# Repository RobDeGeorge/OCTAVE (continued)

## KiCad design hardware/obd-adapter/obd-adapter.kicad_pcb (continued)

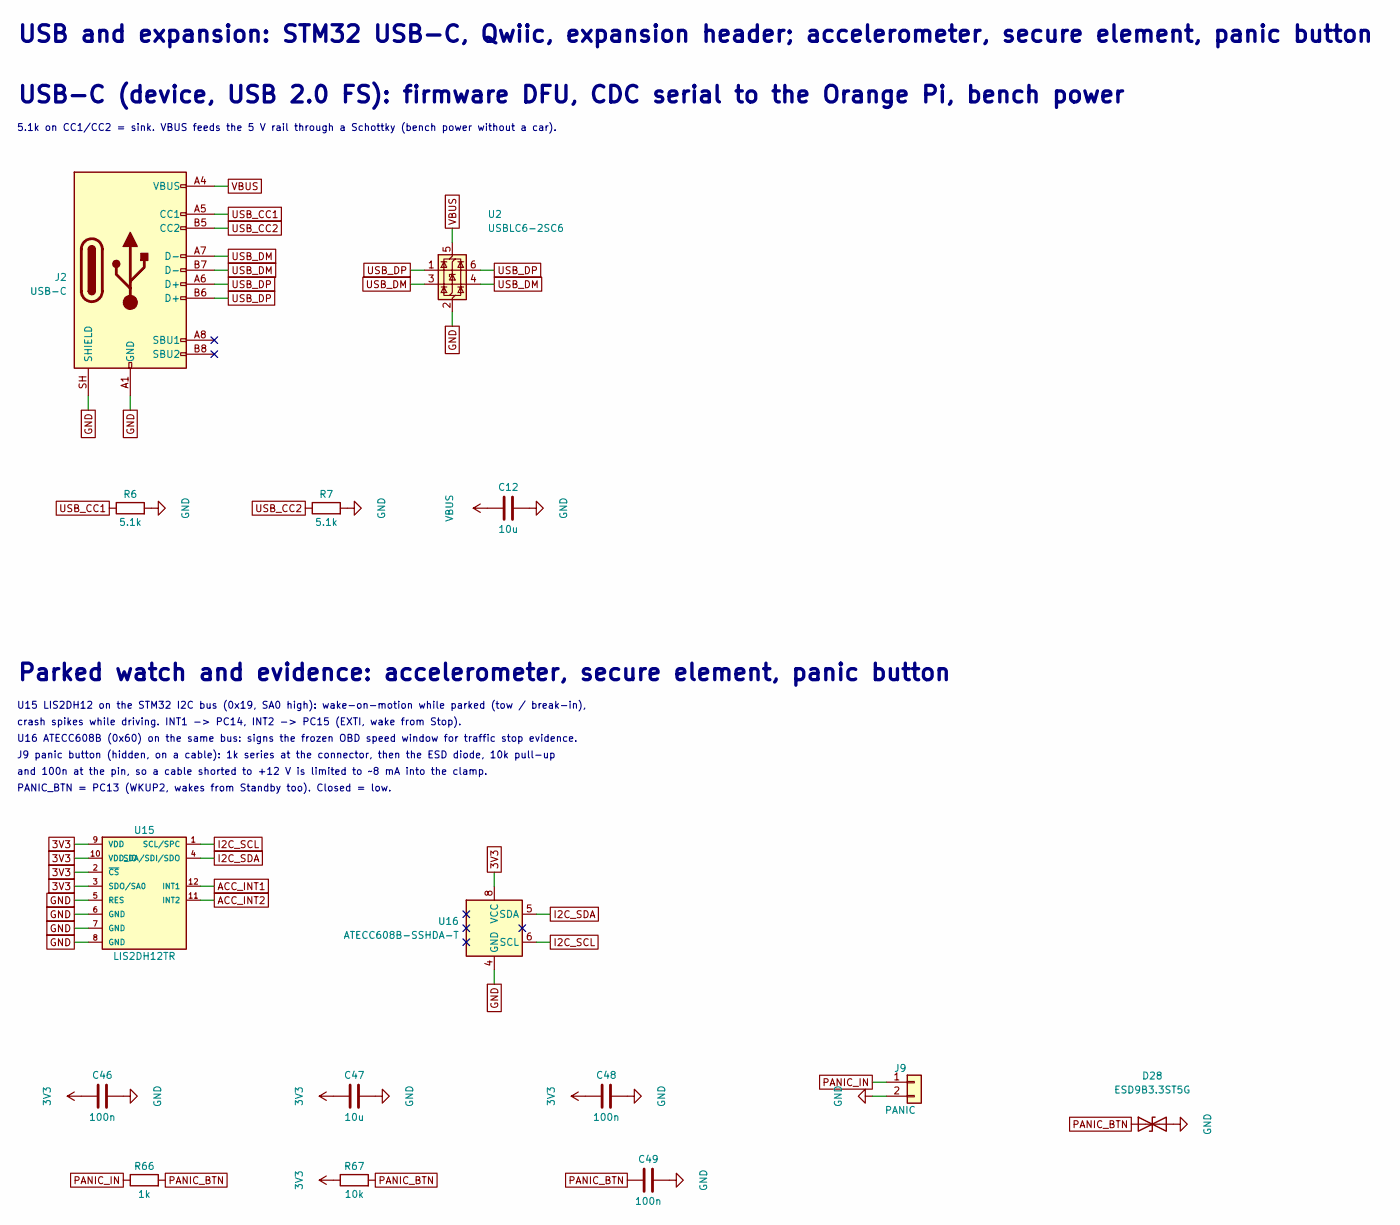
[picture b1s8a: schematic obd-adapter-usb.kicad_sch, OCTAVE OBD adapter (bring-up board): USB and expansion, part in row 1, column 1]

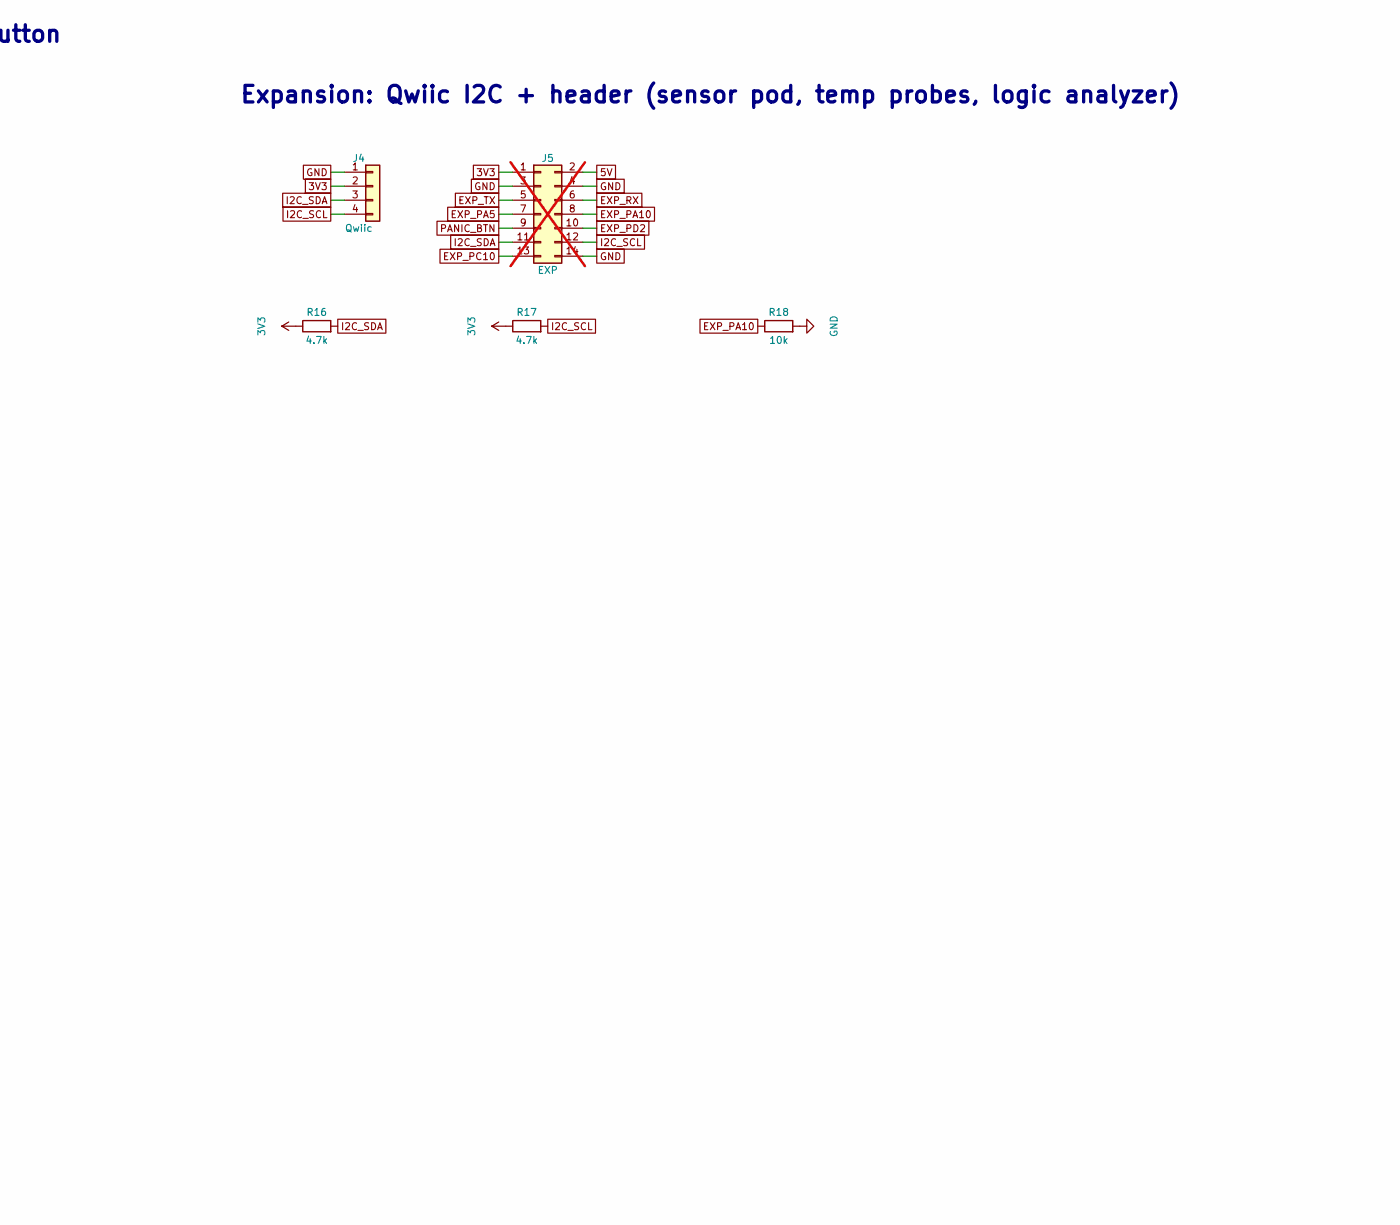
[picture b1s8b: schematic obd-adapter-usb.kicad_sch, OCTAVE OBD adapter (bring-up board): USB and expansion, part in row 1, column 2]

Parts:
C12, C47: 10u; C_0603_1608Metric; LCSC C96446
C46, C48, C49: 100n; C_0603_1608Metric; LCSC C14663
D28: ESD9B3.3ST5G; D_SOD-923; LCSC C96512
J2: USB-C; USB_C_Receptacle_HRO_TYPE-C-31-M-12; LCSC C165948
J4: Qwiic; JST_SH_SM04B-SRSS-TB_1x04-1MP_P1.00mm_Horizontal; LCSC C160404
J5: EXP; PinHeader_2x07_P2.54mm_Vertical; not fitted
J9: PANIC; JST_SH_SM02B-SRSS-TB_1x02-1MP_P1.00mm_Horizontal; LCSC C160402
R6, R7: 5.1k; R_0603_1608Metric; LCSC C23186
R16, R17: 4.7k; R_0603_1608Metric; LCSC C23162
R18, R67: 10k; R_0603_1608Metric; LCSC C25804
R66: 1k; R_0603_1608Metric; LCSC C21190
U2: USBLC6-2SC6; SOT-23-6; LCSC C2687116
U15: LIS2DH12TR; LGA-12_2x2mm_P0.5mm; LCSC C110926
U16: ATECC608B-SSHDA-T; SOIC-8_3.9x4.9mm_P1.27mm; LCSC C1518769

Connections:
3V3: C46.1, C47.1, C48.1, J4.2, J5.1, R16.1, R17.1, R67.1, U15.2 (~CS), U15.3 (SDO/SA0), U15.9 (VDD), U15.10 (VDD_IO), U16.8 (VCC); also elsewhere on the board
5V: J5.2; also elsewhere on the board
ACC_INT1: U15.12 (INT1); also elsewhere on the board
ACC_INT2: U15.11 (INT2); also elsewhere on the board
EXP_PA5: J5.7; also elsewhere on the board
EXP_PA10: J5.8, R18.1; also elsewhere on the board
EXP_PC10: J5.13; also elsewhere on the board
EXP_PD2: J5.10; also elsewhere on the board
EXP_RX: J5.6; also elsewhere on the board
EXP_TX: J5.5; also elsewhere on the board
GND: C12.2, C46.2, C47.2, C48.2, C49.2, D28.2 (A2), J2.A1 (GND), J2.A12 (GND), J2.B1 (GND), J2.B12 (GND), J2.SH (SHIELD), J4.1, J5.3, J5.4, J5.14, J9.2, R6.2, R7.2, R18.2, U2.2 (GND), U15.5 (RES), U15.6 (GND), U15.7 (GND), U15.8 (GND), U16.4 (GND); also elsewhere on the board
I2C_SCL: J4.4, J5.12, R17.2, U15.1 (SCL/SPC), U16.6 (SCL); also elsewhere on the board
I2C_SDA: J4.3, J5.11, R16.2, U15.4 (SDA/SDI/SDO), U16.5 (SDA); also elsewhere on the board
PANIC_BTN: C49.1, D28.1 (A1), J5.9, R66.2, R67.2; also elsewhere on the board
PANIC_IN: J9.1, R66.1
USB_CC1: J2.A5 (CC1), R6.1
USB_CC2: J2.B5 (CC2), R7.1
USB_DM: J2.A7 (D-), J2.B7 (D-), U2.3 (I/O2), U2.4 (I/O2); also elsewhere on the board
USB_DP: J2.A6 (D+), J2.B6 (D+), U2.1 (I/O1), U2.6 (I/O1); also elsewhere on the board
VBUS: C12.1, J2.A4 (VBUS), J2.A9 (VBUS), J2.B4 (VBUS), J2.B9 (VBUS), U2.5 (VBUS); also elsewhere on the board

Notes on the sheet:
USB and expansion: STM32 USB-C, Qwiic, expansion header; accelerometer, secure element, panic button
USB-C (device, USB 2.0 FS): firmware DFU, CDC serial to the Orange Pi, bench power
5.1k on CC1/CC2 = sink. VBUS feeds the 5 V rail through a Schottky (bench power without a car).
Expansion: Qwiic I2C + header (sensor pod, temp probes, logic analyzer)
Parked watch and evidence: accelerometer, secure element, panic button
U15 LIS2DH12 on the STM32 I2C bus (0x19, SA0 high): wake-on-motion while parked (tow / break-in),
crash spikes while driving. INT1 -> PC14, INT2 -> PC15 (EXTI, wake from Stop).
U16 ATECC608B (0x60) on the same bus: signs the frozen OBD speed window for traffic stop evidence.
J9 panic button (hidden, on a cable): 1k series at the connector, then the ESD diode, 10k pull-up
and 100n at the pin, so a cable shorted to +12 V is limited to ~8 mA into the clamp.
PANIC_BTN = PC13 (WKUP2, wakes from Standby too). Closed = low.

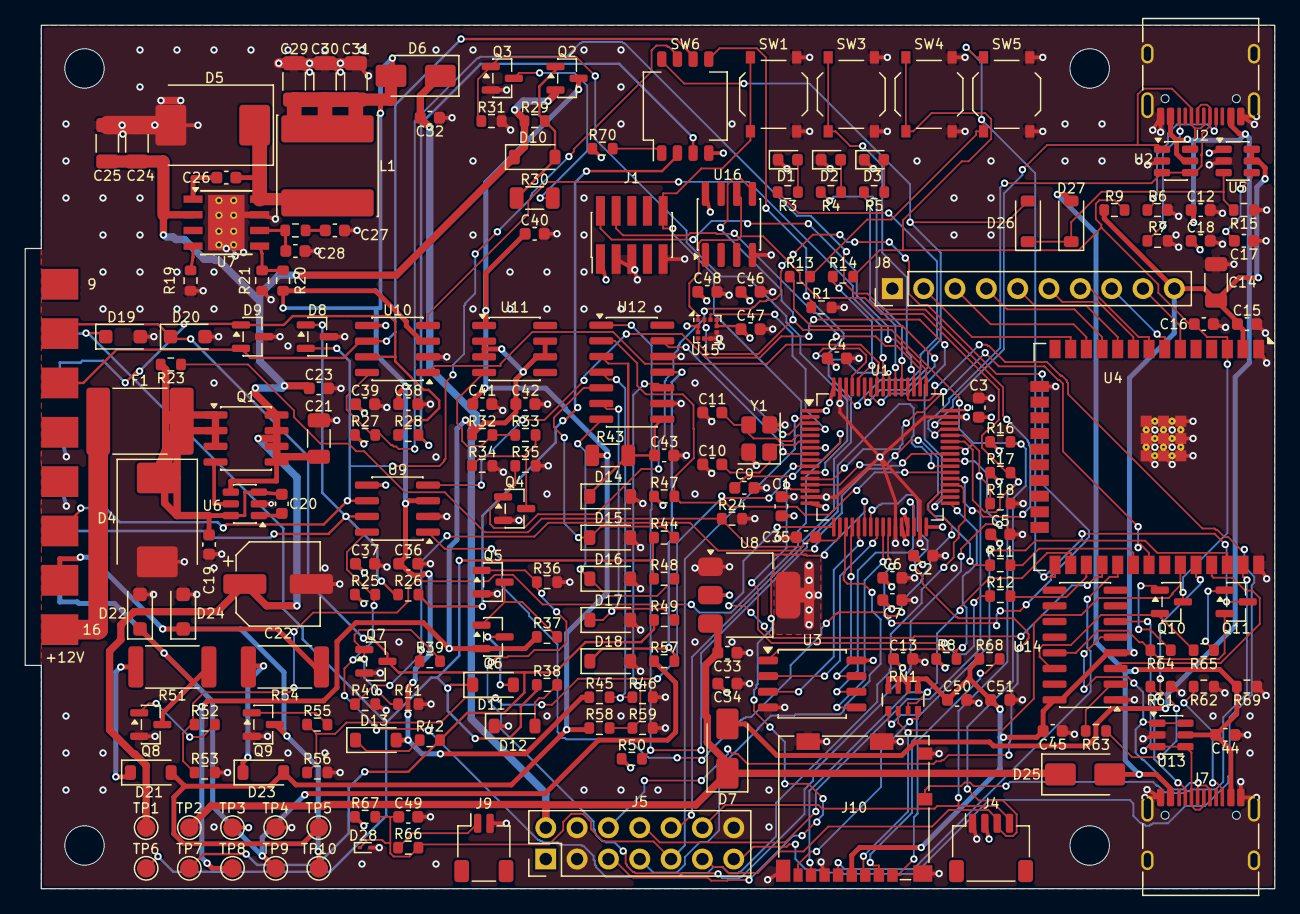
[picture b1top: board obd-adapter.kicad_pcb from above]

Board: 4 copper layers, 101.3 x 70.0 mm, 204 parts (0 on the bottom side), 141 nets.

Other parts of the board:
H1, H2, H3, H4: M3; MountingHole_3.2mm_M3

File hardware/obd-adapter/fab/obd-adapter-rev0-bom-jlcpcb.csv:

Comment,Designator,Footprint,LCSC
100n,"C1,C2,C3,C4,C6,C9,C13,C15,C19,C20,C23,C26,C35,C36,C37,C38,C39,C41,C43,C45,C46,C48,C49,C51",C_0603_1608Metric,C14663
10p,"C10,C11",C_0603_1608Metric,C1634
10u,"C12,C32,C33,C34,C44,C47,C50",C_0603_1608Metric,C96446
22u,C14,C_1206_3216Metric,C12891
1n,C17,C_0603_1608Metric,C1588
10u,C21,C_1206_3216Metric,C13585
47u 50V,C22,CP_Elec_6.3x7.7,C2887275
2.2u,"C24,C25",C_1206_3216Metric,C50254
6.8n,C27,C_0603_1608Metric,C1631
47p,C28,C_0603_1608Metric,C1671
47u,"C29,C30,C31",C_1206_3216Metric,C96123
4.7u,C5,C_0603_1608Metric,C19666
1u,"C7,C16,C18,C40,C42",C_0603_1608Metric,C15849
red,D1,LED_0603_1608Metric,C2286
BZT52C12,D10,D_SOD-123,C19077410
B5819W,"D11,D12,D13",D_SOD-123,C8598
BZT52C33,D14,D_SOD-123,C173417
1N4148W,"D15,D16,D17,D18,D21,D23,D26,D27",D_SOD-123,C81598
SMF24A,"D19,D20,D22,D24",D_SOD-123F,C19077514
green,D2,LED_0603_1608Metric,C12624
ESD9B3.3ST5G,D28,D_SOD-923,C96512
blue,D3,LED_0603_1608Metric,C2288
5.0SMDJ26CA,D4,D_SMC,C444401
B560C,D5,D_SMC,C85100
SS34,"D6,D7,D25",D_SMA,C8678
SZNUP2105L,"D8,D9",SOT-23,C233494
2A 60V,F1,Fuse_2920_7451Metric,C49326266
SWD,J1,PinHeader_2x05_P1.27mm_Vertical_SMD,C41376037
microSD,J10,microSD_HC_Molex_104031-0811,C585350
USB-C,J2,USB_C_Receptacle_HRO_TYPE-C-31-M-12,C165948
Qwiic,J4,JST_SH_SM04B-SRSS-TB_1x04-1MP_P1.00mm_Horizontal,C160404
USB-C ESP32,J7,USB_C_Receptacle_HRO_TYPE-C-31-M-12,C165948
PANIC,J9,JST_SH_SM02B-SRSS-TB_1x02-1MP_P1.00mm_Horizontal,C160402
8.2u,L1,L_Changjiang_FNR8065S,C96978
AO4264E,Q1,SOIC-8_3.9x4.9mm_P1.27mm,C334232
SI2309CDS,Q2,SOT-23,C10493
2N7002,"Q3,Q4,Q5",SOT-23,C8545
AO3401A,Q6,SOT-23,C15127
MMBT3904,"Q7,Q8,Q9,Q10,Q11",SOT-23,C20526
10k,"R1,R8,R9,R18,R35,R36,R38,R42,R44,R47,R48,R49,R50,R57,R58,R59,R64,R65,R67,R68",R_0603_1608Metric,C25804
100k,"R15,R31,R40,R53,R56",R_0603_1608Metric,C25803
4.7k,"R16,R17,R25,R27",R_0603_1608Metric,C23162
160k,R19,R_0603_1608Metric,C22813
68k,R20,R_0603_1608Metric,C23231
12k,R21,R_0603_1608Metric,C22790
13k,R22,R_0603_1608Metric,C22797
100k 0.1%,R23,R_0603_1608Metric,C122538
10k 0.1%,R24,R_0603_1608Metric,C95204
120,"R26,R28",R_0603_1608Metric,C22787
47k,"R29,R46",R_0603_1608Metric,C25819
1k,"R3,R11,R12,R13,R14,R39,R63,R66,R69,R70",R_0603_1608Metric,C21190
10k,R30,R_1206_3216Metric,C17902
240,R32,R_0603_1608Metric,C23350
680,R33,R_0603_1608Metric,C23228
470,"R34,R52,R55",R_0603_1608Metric,C23179
1.5k,R37,R_0603_1608Metric,C22843
330,"R4,R5",R_0603_1608Metric,C23138
2.2k,R41,R_0603_1608Metric,C4190
470,R43,R_1206_3216Metric,C4502
18k,R45,R_0603_1608Metric,C25810
510 2W,"R51,R54",R_2512_6332Metric,C5843118
5.1k,"R6,R7,R61,R62",R_0603_1608Metric,C23186
4x10k,RN1,R_Array_Convex_4x0603,C29718
RESET,SW1,SW_Push_1P1T_XKB_TS-1187A,C318884
USER,SW3,SW_Push_1P1T_XKB_TS-1187A,C318884
ESP_RST,SW4,SW_Push_1P1T_XKB_TS-1187A,C318884
ESP_BOOT,SW5,SW_Push_1P1T_XKB_TS-1187A,C318884
CONFIG,SW6,SW_DIP_SPSTx04_Slide_KingTek_DSHP04TS_W7.62mm_P1.27mm,C40736
STM32G474RET6,U1,LQFP-64_10x10mm_P0.5mm,C521608
LM317LIDR,U11,SOIC-8_3.9x4.9mm_P1.27mm,C183332
LM2901BIDR,U12,SOIC-14_3.9x8.7mm_P1.27mm,C22427890
CH340C,U14,SOIC-16_3.9x9.9mm_P1.27mm,C84681
LIS2DH12TR,U15,LGA-12_2x2mm_P0.5mm,C110926
ATECC608B-SSHDA-T,U16,SOIC-8_3.9x4.9mm_P1.27mm,C1518769
USBLC6-2SC6,"U2,U13",SOT-23-6,C2687116
W25Q128JVSIQ,U3,SOIC-8_5.3x5.3mm_P1.27mm,C97521
ESP32-WROOM-32E-N8,U4,ESP32-WROOM-32E,C701342
TPS22918,U5,SOT-23-6,C131941
LM74700QDBVRQ1,U6,SOT-23-6,C2941042
TPS54360BDDAR,U7,TI_SO-PowerPAD-8_ThermalVias,C524806
AP2114H-3.3,U8,SOT-223-3_TabPin2,C150716
TCAN1044VDRQ1,"U9,U10",SOIC-8_3.9x4.9mm_P1.27mm,C1852061
16MHz,Y1,Crystal_SMD_3225-4Pin_3.2x2.5mm,C13738

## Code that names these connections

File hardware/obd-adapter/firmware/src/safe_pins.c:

#include "safe_pins.h"

#include "board_pins.h"

#define P(net, rev0, nucleo) { PIN_##net, #net, { rev0, nucleo } }

/* "REVIEW" is ../verify/REVIEW.md, section "Firmware obligations (all rounds)".
 *
 * Hardware already holds every bus driver off while a pin is high impedance (pull-downs on the
 * gates and bases, the transceivers' own STB pull-ups), so reset, a blank chip and the ROM bootloader
 * are safe. This table makes the same state explicit and readable, in an order that never passes
 * through an unsafe one. The Nucleo column drives the same pins the same way wherever the Nucleo has
 * nothing of its own on them, so the levels can be measured on its headers. */
const struct safe_pin safe_pins[] = {
    /* Legacy-bus supply first: DLC_SW off (2N7002 gate, 100k to GND on the board). Off = no J1850
     * supply, no comparator supply, no K / L pull-ups: the board draws nothing from those bus pins. */
    P(DLC_SW_EN, PIN_OUT_LOW, PIN_OUT_LOW),

    /* J1850 drivers idle: TXP low = Bus+ P-FET off, TXN low = Bus- sink off. VSEL low = the 7.24 V
     * VPW supply setting (high shorts the 470R for 4.79 V PWM); it only matters with DLC_SW on. */
    P(J1850_TXP, PIN_OUT_LOW, PIN_OUT_LOW),
    P(J1850_TXN, PIN_OUT_LOW, PIN_OUT_LOW),
    P(J1850_VSEL, PIN_OUT_LOW, PIN_OUT_LOW),

    /* K and L line sinks off: TX high pulls the line low through the NPN, so idle is low.
     * REVIEW: "Set LPUART1 TXINV before switching PC1 to its alternate function": PC1 stays a GPIO
     * at low here; kline.c is the only place that hands it to LPUART1, after TXINV. */
    P(KLINE_TX, PIN_OUT_LOW, PIN_OUT_LOW),
    P(LLINE_TX, PIN_OUT_LOW, PIN_OUT_LOW),

    /* REVIEW: "put PB4/PB13 in AF (TXD high) before driving STB low. Never drive STB low while TXD
     * is low." TXD is driven high as a GPIO first, then STB high (standby). This firmware never
     * gives TXD to the FDCAN at all (it only listens), so TXD is high whenever STB is low. */
    P(CAN1_TXD, PIN_OUT_HIGH, PIN_OUT_HIGH),
    P(CAN1_STB, PIN_OUT_HIGH, PIN_OUT_HIGH),
    P(CAN2_TXD, PIN_OUT_HIGH, PIN_OUT_HIGH),
    P(CAN2_STB, PIN_OUT_HIGH, PIN_OUT_HIGH),
    P(CAN1_RXD, PIN_INPUT, PIN_INPUT),
    P(CAN2_RXD, PIN_INPUT, PIN_INPUT),

    /* REVIEW item 23: "Keep PA1/PA2/PB5/PB7 low or as inputs until the ESP32 is powered, and drive
     * ESP_EN open-drain." All six ESP32 lines are inputs here and nothing in this firmware makes
     * the UART lines outputs. PB7 (EN) is only ever pulled low open-drain (board_esp_reset()).
     * REVIEW: "Leave PB5 (IO0) and PB7 (EN) as inputs while the ESP32 is being flashed through J7."
     * On the Nucleo PA2 / PA3 are the ST-LINK serial port; uart.c takes them after this table. */
    P(ESP_RTS, PIN_INPUT, PIN_INPUT),
    P(ESP_CTS_M, PIN_INPUT, PIN_INPUT),
    P(MCU_TX_ESP_M, PIN_INPUT, PIN_INPUT),
    P(ESP_TX_MCU, PIN_INPUT, PIN_INPUT),
    P(ESP_IO0_M, PIN_INPUT, PIN_INPUT),
    P(ESP_EN_M, PIN_INPUT, PIN_INPUT),
    /* PB6: the ESP32 load switch, OR'd with CONFIG switch 1 (3V3 through 1k) and VBUS2. As an input
     * with the pull-down the switch decides ("esp auto"); PB6 then reads the switch position. */
    P(ESP_PWR_EN, PIN_INPUT_PULLDOWN, PIN_ANALOG),

    /* REVIEW round 6: "Turn on PC0's pull-up before enabling LPUART1's receiver" (KLINE_RX is an
     * open-collector output with no resistor on the board). On from the start. */
    P(KLINE_RX, PIN_INPUT_PULLUP, PIN_INPUT_PULLUP),
    /* J1850 comparator outputs, 10k pull-ups on the board. Inputs until there is a J1850 codec. */
    P(VPW_RX, PIN_INPUT, PIN_INPUT),
    P(PWM_RX, PIN_INPUT, PIN_INPUT),

    /* REVIEW round 6: "keep PA15's pull-up on when the pin becomes a GPIO (it is on from reset, as
     * JTDI; a plain input without PUPDR set would float)". gpio_input() writes the pull before the mode. */
    P(BTN_USER, PIN_INPUT_PULLUP, PIN_INPUT_PULLUP),
    /* PC13: PANIC button, 10k pull-up on the board, closed = low. Nucleo: B1, pressed = high, its own
     * pull-down. No internal pull on either. */
    P(PANIC_BTN, PIN_INPUT, PIN_INPUT),
    /* REVIEW round 5: no 32 kHz crystal, PC14 / PC15 are the accelerometer's interrupt outputs (push-pull,
     * active high). The pull-downs give a level if U15 is not fitted. Nucleo: the LSE crystal, left alone. */
    P(ACC_INT1, PIN_INPUT_PULLDOWN, PIN_SYSTEM),
    P(ACC_INT2, PIN_INPUT_PULLDOWN, PIN_SYSTEM),
    /* PB8 is BOOT0 at reset (10k to GND; CONFIG switch 4 ties it to 3V3). Read as an input, to warn. */
    P(BOOT0, PIN_INPUT, PIN_INPUT),

    /* LEDs: pin -> resistor -> LED -> GND, on = high */
    P(LED_R, PIN_OUT_LOW, PIN_OUT_LOW),
    P(LED_G, PIN_OUT_LOW, PIN_OUT_LOW),
    P(LED_B, PIN_OUT_LOW, PIN_OUT_LOW),

    /* taken later by their drivers: adc.c, i2c.c (4.7k pull-ups on the board), uart.c (rev0 console) */
    P(VBAT_SENSE, PIN_ANALOG, PIN_ANALOG),
    P(I2C_SDA, PIN_ANALOG, PIN_ANALOG),
    P(I2C_SCL, PIN_ANALOG, PIN_ANALOG),
    P(EXP_TX, PIN_ANALOG, PIN_ANALOG),
    P(EXP_RX, PIN_ANALOG, PIN_ANALOG),

    /* QSPI flash: not used yet. NCS has a 10k pull-up on the board, so the flash stays deselected.
     * REVIEW: "Set the W25Q128 QE bit before using quad mode" applies to the driver that is not here. */
    P(QSPI_NCS, PIN_ANALOG, PIN_ANALOG),
    P(QSPI_CLK, PIN_ANALOG, PIN_ANALOG),
    P(QSPI_IO0, PIN_ANALOG, PIN_ANALOG),
    P(QSPI_IO1, PIN_ANALOG, PIN_ANALOG),
    P(QSPI_IO2, PIN_ANALOG, PIN_ANALOG),
    P(QSPI_IO3, PIN_ANALOG, PIN_ANALOG),

    /* USB: the reset state. No USB stack in this firmware; the ROM bootloader (DFU) does its own. */
    P(USB_DM, PIN_ANALOG, PIN_ANALOG),
    P(USB_DP, PIN_ANALOG, PIN_ANALOG),

    /* spare pins on J5. PA5 is LD2 on the Nucleo. */
    P(EXP_PA5, PIN_ANALOG, PIN_OUT_LOW),
    P(EXP_PA10, PIN_ANALOG, PIN_ANALOG),
    P(EXP_PC10, PIN_ANALOG, PIN_ANALOG),
    P(EXP_PD2, PIN_ANALOG, PIN_ANALOG),

    /* debug port, oscillator, reset */
    P(SWDIO, PIN_SYSTEM, PIN_SYSTEM),
    P(SWCLK, PIN_SYSTEM, PIN_SYSTEM),
    P(HSE_IN, PIN_SYSTEM, PIN_SYSTEM),
    P(HSE_OUT, PIN_SYSTEM, PIN_SYSTEM),
    P(NRST, PIN_SYSTEM, PIN_SYSTEM),
};

const unsigned safe_pins_count = sizeof safe_pins / sizeof safe_pins[0];

const char *pin_state_name(enum pin_state state)
{
    switch (state) {
    case PIN_SYSTEM:         return "system";
    case PIN_ANALOG:         return "analog";
    case PIN_INPUT:          return "input";
    case PIN_INPUT_PULLUP:   return "input pull-up";
    case PIN_INPUT_PULLDOWN: return "input pull-down";
    case PIN_OUT_LOW:        return "out low";
    case PIN_OUT_HIGH:       return "out high";
    }
    return "?";
}

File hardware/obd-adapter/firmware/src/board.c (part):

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
void board_force_safe(void)
{
    gpio_output(PIN_DLC_SW_EN, false);
    gpio_output(PIN_J1850_TXP, false);
    gpio_output(PIN_J1850_TXN, false);
    gpio_output(PIN_KLINE_TX, false);
    gpio_output(PIN_LLINE_TX, false);
    /* REVIEW: never STB low while TXD is low. TXD high first, then standby. */
    gpio_output(PIN_CAN1_TXD, true);
    gpio_output(PIN_CAN1_STB, true);
    gpio_output(PIN_CAN2_TXD, true);
    gpio_output(PIN_CAN2_STB, true);
}

unsigned board_check_outputs(void (*report)(const struct safe_pin *pin, bool driven, bool read))
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
void led_set(bool red, bool green, bool blue)
{
    gpio_write(PIN_LED_R, red);
    gpio_write(PIN_LED_G, green);
    gpio_write(PIN_LED_B, blue);
#if defined(BOARD_NUCLEO)
    gpio_write(PIN_EXP_PA5, red || green || blue); /* LD2: the Nucleo's one LED shows any colour */
#endif
}

bool board_button(void)
{
#if defined(BOARD_NUCLEO)
    return gpio_read(PIN_PANIC_BTN); /* B1 on PC13: pressed = high */
#else
    return !gpio_read(PIN_BTN_USER); /* SW3 on PA15 to GND: pressed = low */
#endif
}

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{
    if (!on) {
        /* the drivers that DLC_SW feeds go idle before their supply does */
        gpio_output(PIN_J1850_TXP, false);
        gpio_output(PIN_J1850_TXN, false);
        gpio_output(PIN_KLINE_TX, false);
        gpio_output(PIN_LLINE_TX, false);
    }
    gpio_write(PIN_DLC_SW_EN, on);
}

bool board_dlc_is_on(void)
{
    return gpio_latch(PIN_DLC_SW_EN);
}

/* ------------------------------------------------------------------ ESP32 power and reset */
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void board_esp_mode(enum esp_mode mode)
{
#if BOARD_HAS_ESP32
    /* REVIEW item 23: only PB6 changes here. The six signal pins stay inputs whatever the mode, so
     * nothing can back-power the module through a signal pin while its rail is off. */
    switch (mode) {
    case ESP_AUTO:
        gpio_input(PIN_ESP_PWR_EN, GPIO_PULL_DOWN);
        break;
    case ESP_ON:
        gpio_output(PIN_ESP_PWR_EN, true);
        break;
    case ESP_OFF:
        /* with CONFIG switch 1 on this sinks 3.3 mA through R70 (1k): allowed for by the design */
        gpio_output(PIN_ESP_PWR_EN, false);
        break;
    }
    esp_mode_now = mode;
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bool board_esp_rail_up(void)
{
#if BOARD_HAS_ESP32
    /* EN has 10k to 3V3_ESP on the module side of the 1k series resistor: with PB7 an input it reads
     * the rail. (Low also while SW4 is held or the USB bridge holds the ESP32 in reset.) */
    return gpio_read(PIN_ESP_EN_M);
#else
    return false;
#endif
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void board_esp_reset(void)
{
#if BOARD_HAS_ESP32
    /* REVIEW item 23: "drive ESP_EN open-drain". The latch is low and the pin open drain before it
     * becomes an output; it is never driven high. REVIEW: PB7 goes back to an input afterwards, so the
     * auto-reset circuit of the USB bridge (J7) has the line to itself. */
    gpio_output_open_drain(PIN_ESP_EN_M, false);
    delay_ms(20);
    gpio_write(PIN_ESP_EN_M, true);
    gpio_input(PIN_ESP_EN_M, GPIO_PULL_NONE);
    gpio_set_open_drain(PIN_ESP_EN_M, false);
#endif
}

/* ------------------------------------------------------------------ EXTI
 *
 * REVIEW round 5: "one pin per EXTI line". Line n can be pin n of one port only, so PA15 (USER) and
 * PC15 (accelerometer INT2) cannot both interrupt: INT2 is not used as an interrupt, accelerometer
 * events go to INT1 (PC14). Line 3 (PA3 or PB3) and line 0 (PA0 or PC0) are free here.
 *
 * X(line, pin, rising edge, falling edge, name) */
#if defined(BOARD_REV0)
#define EXTI_OWNERS(X)                                   \
    X(13, PIN_PANIC_BTN, 0, 1, "PANIC button (J9)")      \
    X(14, PIN_ACC_INT1, 1, 0, "accelerometer INT1")      \
    X(15, PIN_BTN_USER, 0, 1, "USER button")
#else
#define EXTI_OWNERS(X) X(13, PIN_PANIC_BTN, 1, 0, "B1 button")
#endif

/* a second entry for a line that already has one declares the same enumerator twice: a compile error */
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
